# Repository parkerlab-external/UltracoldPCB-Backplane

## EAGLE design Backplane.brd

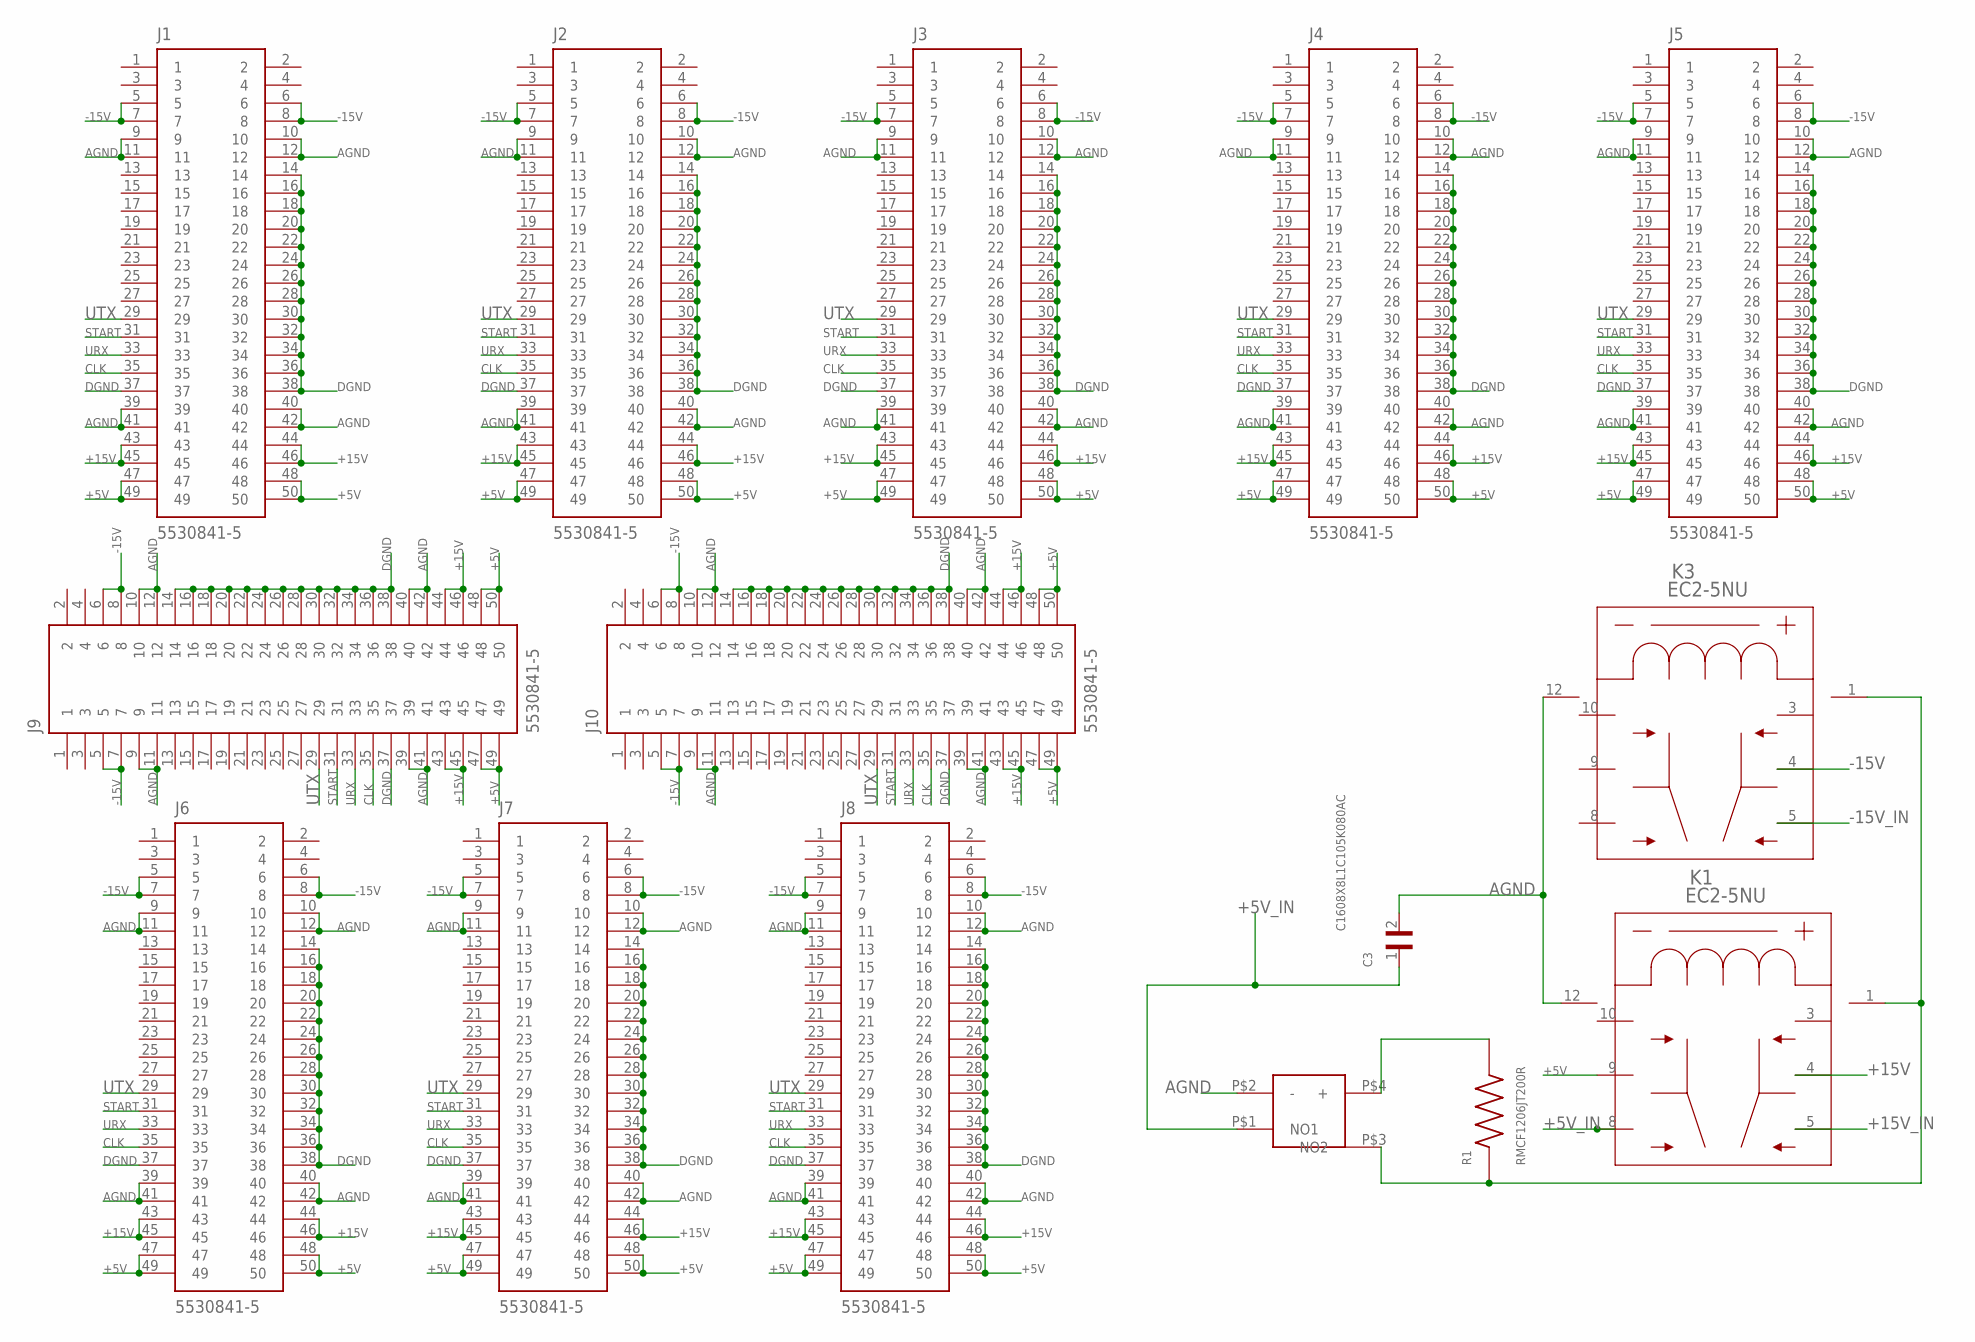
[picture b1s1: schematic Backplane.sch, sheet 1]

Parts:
C3: C1608X8L1C105K080AC; CAPC1608X90N
J1, J2, J3, J4, J5, J6, J7, J8, J9, J10: 5530841-5; TE_5530841-5
K1, K3: EC2-5NU; EC2NU
R1: RMCF1206JT200R; RESC3216X70N
U$1: BUTTON_DEV; BUTTON_FOOT

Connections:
+5V: J1.47, J1.48, J1.49, J1.50, J2.47, J2.48, J2.49, J2.50, J3.47, J3.48, J3.49, J3.50, J4.47, J4.48, J4.49, J4.50, J5.47, J5.48, J5.49, J5.50, J6.47, J6.48, J6.49, J6.50, J7.47, J7.48, J7.49, J7.50, J8.47, J8.48, J8.49, J8.50, J9.47, J9.48, J9.49, J9.50, J10.47, J10.48, J10.49, J10.50, K1.9 (6)
+5V_IN: C3.1, K1.8 (5), U$1.P$1 (NO1); also elsewhere on the board
+15V: J1.43, J1.44, J1.45, J1.46, J2.43, J2.44, J2.45, J2.46, J3.43, J3.44, J3.45, J3.46, J4.43, J4.44, J4.45, J4.46, J5.43, J5.44, J5.45, J5.46, J6.43, J6.44, J6.45, J6.46, J7.43, J7.44, J7.45, J7.46, J8.43, J8.44, J8.45, J8.46, J9.43, J9.44, J9.45, J9.46, J10.43, J10.44, J10.45, J10.46, K1.4 (3)
+15V_IN: K1.5 (4); also elsewhere on the board
-15V: J1.5, J1.6, J1.7, J1.8, J2.5, J2.6, J2.7, J2.8, J3.5, J3.6, J3.7, J3.8, J4.5, J4.6, J4.7, J4.8, J5.5, J5.6, J5.7, J5.8, J6.5, J6.6, J6.7, J6.8, J7.5, J7.6, J7.7, J7.8, J8.5, J8.6, J8.7, J8.8, J9.5, J9.6, J9.7, J9.8, J10.5, J10.6, J10.7, J10.8, K3.4 (3)
-15V_IN: K3.5 (4); also elsewhere on the board
AGND: C3.2, J1.9, J1.10, J1.11, J1.12, J1.39, J1.40, J1.41, J1.42, J2.9, J2.10, J2.11, J2.12, J2.39, J2.40, J2.41, J2.42, J3.9, J3.10, J3.11, J3.12, J3.39, J3.40, J3.41, J3.42, J4.9, J4.10, J4.11, J4.12, J4.39, J4.40, J4.41, J4.42, J5.9, J5.10, J5.11, J5.12, J5.39, J5.40, J5.41, J5.42, J6.9, J6.10, J6.11, J6.12, J6.39, J6.40, J6.41, J6.42, J7.9, J7.10, J7.11, J7.12, J7.39, J7.40, J7.41, J7.42, J8.9, J8.10, J8.11, J8.12, J8.39, J8.40, J8.41, J8.42, J9.9, J9.10, J9.11, J9.12, J9.39, J9.40, J9.41, J9.42, J10.9, J10.10, J10.11, J10.12, J10.39, J10.40, J10.41, J10.42, K1.12 (8), K3.12 (8), U$1.P$2 (-); also elsewhere on the board
CLK: J1.35, J2.35, J3.35, J4.35, J5.35, J6.35, J7.35, J8.35, J9.35, J10.35; also elsewhere on the board
DGND: J1.14, J1.16, J1.18, J1.20, J1.22, J1.24, J1.26, J1.28, J1.30, J1.32, J1.34, J1.36, J1.37, J1.38, J2.14, J2.16, J2.18, J2.20, J2.22, J2.24, J2.26, J2.28, J2.30, J2.32, J2.34, J2.36, J2.37, J2.38, J3.14, J3.16, J3.18, J3.20, J3.22, J3.24, J3.26, J3.28, J3.30, J3.32, J3.34, J3.36, J3.37, J3.38, J4.14, J4.16, J4.18, J4.20, J4.22, J4.24, J4.26, J4.28, J4.30, J4.32, J4.34, J4.36, J4.37, J4.38, J5.14, J5.16, J5.18, J5.20, J5.22, J5.24, J5.26, J5.28, J5.30, J5.32, J5.34, J5.36, J5.37, J5.38, J6.14, J6.16, J6.18, J6.20, J6.22, J6.24, J6.26, J6.28, J6.30, J6.32, J6.34, J6.36, J6.37, J6.38, J7.14, J7.16, J7.18, J7.20, J7.22, J7.24, J7.26, J7.28, J7.30, J7.32, J7.34, J7.36, J7.37, J7.38, J8.14, J8.16, J8.18, J8.20, J8.22, J8.24, J8.26, J8.28, J8.30, J8.32, J8.34, J8.36, J8.37, J8.38, J9.14, J9.16, J9.18, J9.20, J9.22, J9.24, J9.26, J9.28, J9.30, J9.32, J9.34, J9.36, J9.37, J9.38, J10.14, J10.16, J10.18, J10.20, J10.22, J10.24, J10.26, J10.28, J10.30, J10.32, J10.34, J10.36, J10.37, J10.38; also elsewhere on the board
unnamed: R1.2, U$1.P$4 (+)
unnamed: K1.1, K3.1, R1.1, U$1.P$3 (NO2)
START: J1.31, J2.31, J3.31, J4.31, J5.31, J6.31, J7.31, J8.31, J9.31, J10.31; also elsewhere on the board
URX: J1.33, J2.33, J3.33, J4.33, J5.33, J6.33, J7.33, J8.33, J9.33, J10.33; also elsewhere on the board
UTX: J1.29, J2.29, J3.29, J4.29, J5.29, J6.29, J7.29, J8.29, J9.29, J10.29; also elsewhere on the board

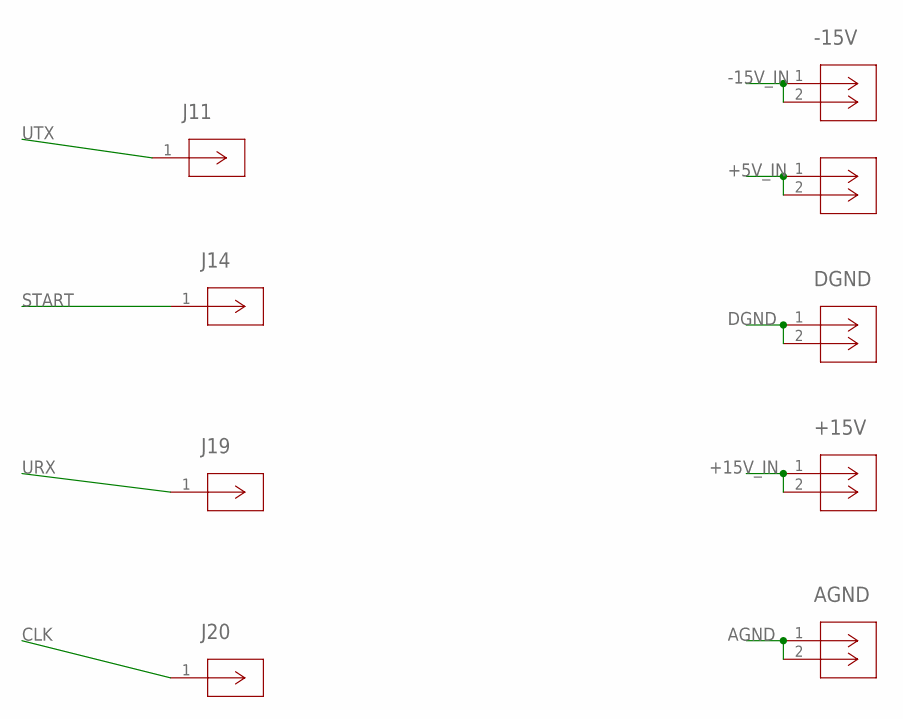
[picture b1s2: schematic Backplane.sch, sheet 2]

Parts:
+5V, +15V: 24.243.1; CONN_24.243_MTC
-15V: 24.243.1; CONN_24.243_MTC
AGND: 24.243.1; CONN_24.243_MTC
DGND: 24.243.1; CONN_24.243_MTC
J11, J14, J19, J20: 112404; CONN_112404_AMP

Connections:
+5V_IN: +5V.1, +5V.2; also elsewhere on the board
+15V_IN: +15V.1, +15V.2; also elsewhere on the board
-15V_IN: -15V.1, -15V.2; also elsewhere on the board
AGND: AGND.1, AGND.2; also elsewhere on the board
CLK: J20.1; also elsewhere on the board
DGND: DGND.1, DGND.2; also elsewhere on the board
START: J14.1; also elsewhere on the board
URX: J19.1; also elsewhere on the board
UTX: J11.1; also elsewhere on the board

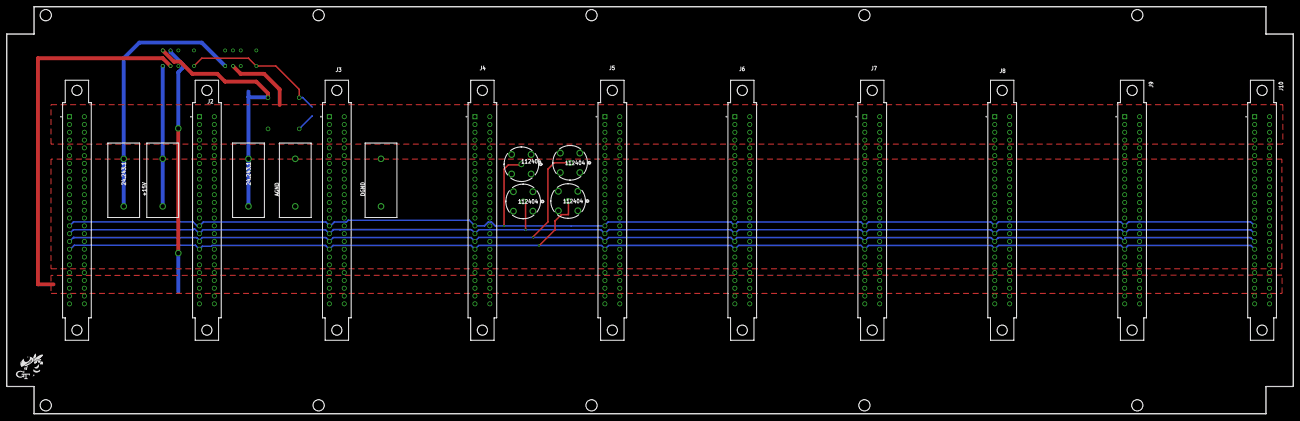
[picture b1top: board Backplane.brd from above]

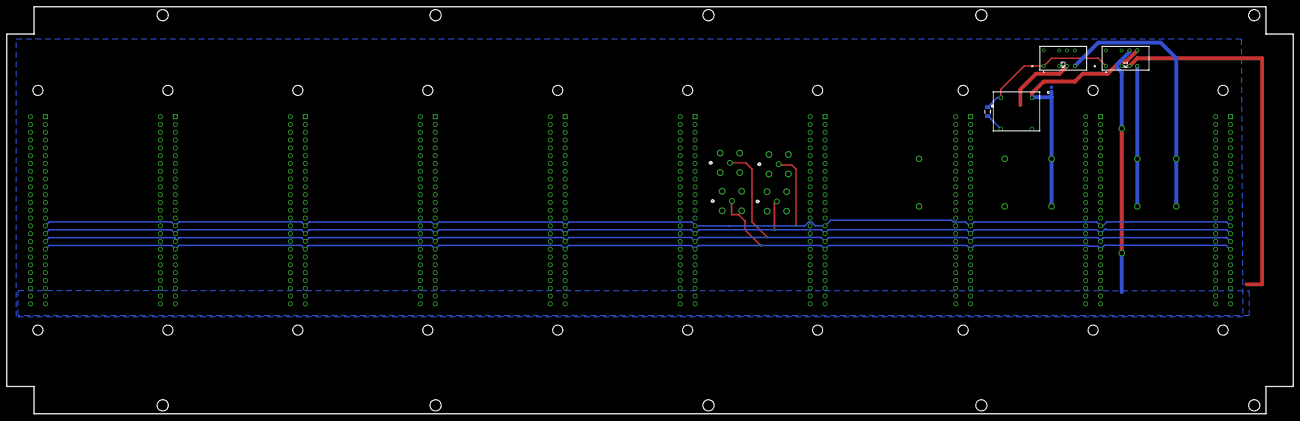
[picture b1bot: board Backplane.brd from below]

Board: 2 copper layers, 419.1 x 132.6 mm, 25 parts (5 on the bottom side), 14 nets.

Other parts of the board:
DRILEGEND: DRILEGEND

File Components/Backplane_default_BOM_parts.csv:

"Part","Value","Device","Package","Library","Description","BUILT_BY","COIL_RESISTANCE","COIL_TYPE","COMMENT","CONTACT_CONFIGURATION","CONTACT_CURRENT","CONTACT_VOLTAGE_DC","CONTACT_VOLTAGE_VAC","COPYRIGHT","DATASHEET","DESCRIPTION","DIGI-KEY_PART_NUMBER","DIGI-KEY_PART_NUMBER_1","EU_ROHS_COMPLIANCE","MANUFACTURER_PART_NUMBER","MF","MFR_NAME","MP","MPN","PACKAGE","PURCHASE-URL","SHORTCUT","SOURCELIBRARY","VENDOR",
"+5V","24.243.1","24.243.1","CONN_24.243_MTC","39F1574","","","","","","","","","","Copyright (C) 2022 Ultra Librarian. All rights reserved.","","","","","","24.243.1","","Multicomp","","","","","","","",
"+15V","24.243.1","24.243.1","CONN_24.243_MTC","Banana_connector_24.243.1","","EMA_Justin","","","","","","","","Copyright (C) 2018 Accelerated Designs. All rights reserved","http://www.farnell.com/datasheets/1901211.pdf?_ga=2.20927118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","","","","","24.243.1","","","","","","","","Multicomp_2020-02-25","Multicomp",
"-15V","24.243.1","24.243.1","CONN_24.243_MTC","39F1574","","","","","","","","","","Copyright (C) 2022 Ultra Librarian. All rights reserved.","","","","","","24.243.1","","Multicomp","","","","","","","",
"AGND","24.243.1","24.243.1","CONN_24.243_MTC","Banana_connector_24.243.1","","EMA_Justin","","","","","","","","Copyright (C) 2018 Accelerated Designs. All rights reserved","http://www.farnell.com/datasheets/1901211.pdf?_ga=2.20927118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","","","","","24.243.1","","","","","","","","Multicomp_2020-02-25","Multicomp",
"C3","C1608X8L1C105K080AC","C1608X8L1C105K080AC","CAPC1608X90N","1uF_cap_C1608X8L1C105K080AC","","","","","","","","","","",""," 1µF ±10% 16V Ceramic Capacitor X8L 0603 (1608 Metric) ","445-175407-1-ND","","","","TDK","","C1608X8L1C105K080AC","","1608 TDK","","","","",
"DGND","24.243.1","24.243.1","CONN_24.243_MTC","Banana_connector_24.243.1","","EMA_Justin","","","","","","","","Copyright (C) 2018 Accelerated Designs. All rights reserved","http://www.farnell.com/datasheets/1901211.pdf?_ga=2.20927118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","","","","","24.243.1","","","","","","","","Multicomp_2020-02-25","Multicomp",
"J1","5530841-5","5530841-5","TE_5530841-5","cardEdge5530841-5","Conn Power Card Edge SKT 50 POS 2.54mm Solder ST Thru-Hole","","","","5530841-5","","","","","",""," Conn Power Card Edge SKT 50 POS 2.54mm Solder ST Thru-Hole ","5530841-5-ND","","Compliant","","TE Connectivity","","5530841-5","","None","https://pricing.snapeda.com/search/part/5530841-5/?ref=eda","","","",
"J2","5530841-5","5530841-5","TE_5530841-5","cardEdge5530841-5","Conn Power Card Edge SKT 50 POS 2.54mm Solder ST Thru-Hole","","","","5530841-5","","","","","",""," Conn Power Card Edge SKT 50 POS 2.54mm Solder ST Thru-Hole ","5530841-5-ND","","Compliant","","TE Connectivity","","5530841-5","","None","https://pricing.snapeda.com/search/part/5530841-5/?ref=eda","","","",
"J3","5530841-5","5530841-5","TE_5530841-5","cardEdge5530841-5","Conn Power Card Edge SKT 50 POS 2.54mm Solder ST Thru-Hole","","","","5530841-5","","","","","",""," Conn Power Card Edge SKT 50 POS 2.54mm Solder ST Thru-Hole ","5530841-5-ND","","Compliant","","TE Connectivity","","5530841-5","","None","https://pricing.snapeda.com/search/part/5530841-5/?ref=eda","","","",
"J4","5530841-5","5530841-5","TE_5530841-5","cardEdge5530841-5","Conn Power Card Edge SKT 50 POS 2.54mm Solder ST Thru-Hole","","","","5530841-5","","","","","",""," Conn Power Card Edge SKT 50 POS 2.54mm Solder ST Thru-Hole ","5530841-5-ND","","Compliant","","TE Connectivity","","5530841-5","","None","https://pricing.snapeda.com/search/part/5530841-5/?ref=eda","","","",
"J5","5530841-5","5530841-5","TE_5530841-5","cardEdge5530841-5","Conn Power Card Edge SKT 50 POS 2.54mm Solder ST Thru-Hole","","","","5530841-5","","","","","",""," Conn Power Card Edge SKT 50 POS 2.54mm Solder ST Thru-Hole ","5530841-5-ND","","Compliant","","TE Connectivity","","5530841-5","","None","https://pricing.snapeda.com/search/part/5530841-5/?ref=eda","","","",
"J6","5530841-5","5530841-5","TE_5530841-5","cardEdge5530841-5","Conn Power Card Edge SKT 50 POS 2.54mm Solder ST Thru-Hole","","","","5530841-5","","","","","",""," Conn Power Card Edge SKT 50 POS 2.54mm Solder ST Thru-Hole ","5530841-5-ND","","Compliant","","TE Connectivity","","5530841-5","","None","https://pricing.snapeda.com/search/part/5530841-5/?ref=eda","","","",
"J7","5530841-5","5530841-5","TE_5530841-5","cardEdge5530841-5","Conn Power Card Edge SKT 50 POS 2.54mm Solder ST Thru-Hole","","","","5530841-5","","","","","",""," Conn Power Card Edge SKT 50 POS 2.54mm Solder ST Thru-Hole ","5530841-5-ND","","Compliant","","TE Connectivity","","5530841-5","","None","https://pricing.snapeda.com/search/part/5530841-5/?ref=eda","","","",
"J8","5530841-5","5530841-5","TE_5530841-5","cardEdge5530841-5","Conn Power Card Edge SKT 50 POS 2.54mm Solder ST Thru-Hole","","","","5530841-5","","","","","",""," Conn Power Card Edge SKT 50 POS 2.54mm Solder ST Thru-Hole ","5530841-5-ND","","Compliant","","TE Connectivity","","5530841-5","","None","https://pricing.snapeda.com/search/part/5530841-5/?ref=eda","","","",
"J9","5530841-5","5530841-5","TE_5530841-5","cardEdge5530841-5","Conn Power Card Edge SKT 50 POS 2.54mm Solder ST Thru-Hole","","","","5530841-5","","","","","",""," Conn Power Card Edge SKT 50 POS 2.54mm Solder ST Thru-Hole ","5530841-5-ND","","Compliant","","TE Connectivity","","5530841-5","","None","https://pricing.snapeda.com/search/part/5530841-5/?ref=eda","","","",
"J10","5530841-5","5530841-5","TE_5530841-5","cardEdge5530841-5","Conn Power Card Edge SKT 50 POS 2.54mm Solder ST Thru-Hole","","","","5530841-5","","","","","",""," Conn Power Card Edge SKT 50 POS 2.54mm Solder ST Thru-Hole ","5530841-5-ND","","Compliant","","TE Connectivity","","5530841-5","","None","https://pricing.snapeda.com/search/part/5530841-5/?ref=eda","","","",
"J11","112404","112404","CONN_112404_AMP","39F1574","","","","","","","","","","Copyright (C) 2022 Ultra Librarian. All rights reserved.","","","","ACX1051-ND","","112404","","Amphenol ICC","","","","","","","",
"J14","112404","112404","CONN_112404_AMP","39F1574","","","","","","","","","","Copyright (C) 2022 Ultra Librarian. All rights reserved.","","","","ACX1051-ND","","112404","","Amphenol ICC","","","","","","","",
"J19","112404","112404","CONN_112404_AMP","39F1574","","","","","","","","","","Copyright (C) 2022 Ultra Librarian. All rights reserved.","","","","ACX1051-ND","","112404","","Amphenol ICC","","","","","","","",
"J20","112404","112404","CONN_112404_AMP","39F1574","","","","","","","","","","Copyright (C) 2022 Ultra Librarian. All rights reserved.","","","","ACX1051-ND","","112404","","Amphenol ICC","","","","","","","",
"K1","EC2-5NU","EC2-5NU","EC2NU","EC2-5NU","EC2-5NU :","","178 Ohm","Non Latching","","DPDT","5A","220V","250V","","","","","","","EC25NU","","","","EC2-5NU","","","EC2","","KEMET",
"K3","EC2-5NU","EC2-5NU","EC2NU","EC2-5NU","EC2-5NU :","","178 Ohm","Non Latching","","DPDT","5A","220V","250V","","","","","","","EC25NU","","","","EC2-5NU","","","EC2","","KEMET",
"R1","RMCF1206JT200R","RMCF1206JT200R","RESC3216X70N","200ohm_res_RMCF1206JT200R","","","","","","","","","","",""," 200 Ohms ±5% 0.25W, 1/4W Chip Resistor 1206 (3216 Metric) Automotive AEC-Q200 Thick Film ","RMCF1206JT200RCT-ND","","","","Stackpole Electronics Inc","","RMCF1206JT200R","","3216 Stackpole","","","","",
"U$1","BUTTON_DEV","BUTTON_DEV","BUTTON_FOOT","button_new","","","","","","","","","","","","","","","","","","","","","","","","","",

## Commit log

2025-03-03 PCB Design.

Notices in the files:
parts and their libraries:
COPYRIGHT: Copyright (C) 2018 Accelerated Designs. All rights reserved
COPYRIGHT: Copyright (C) 2022 Ultra Librarian. All rights reserved.
